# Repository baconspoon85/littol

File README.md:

# littol
3 row 30% katana with exploded spacebar

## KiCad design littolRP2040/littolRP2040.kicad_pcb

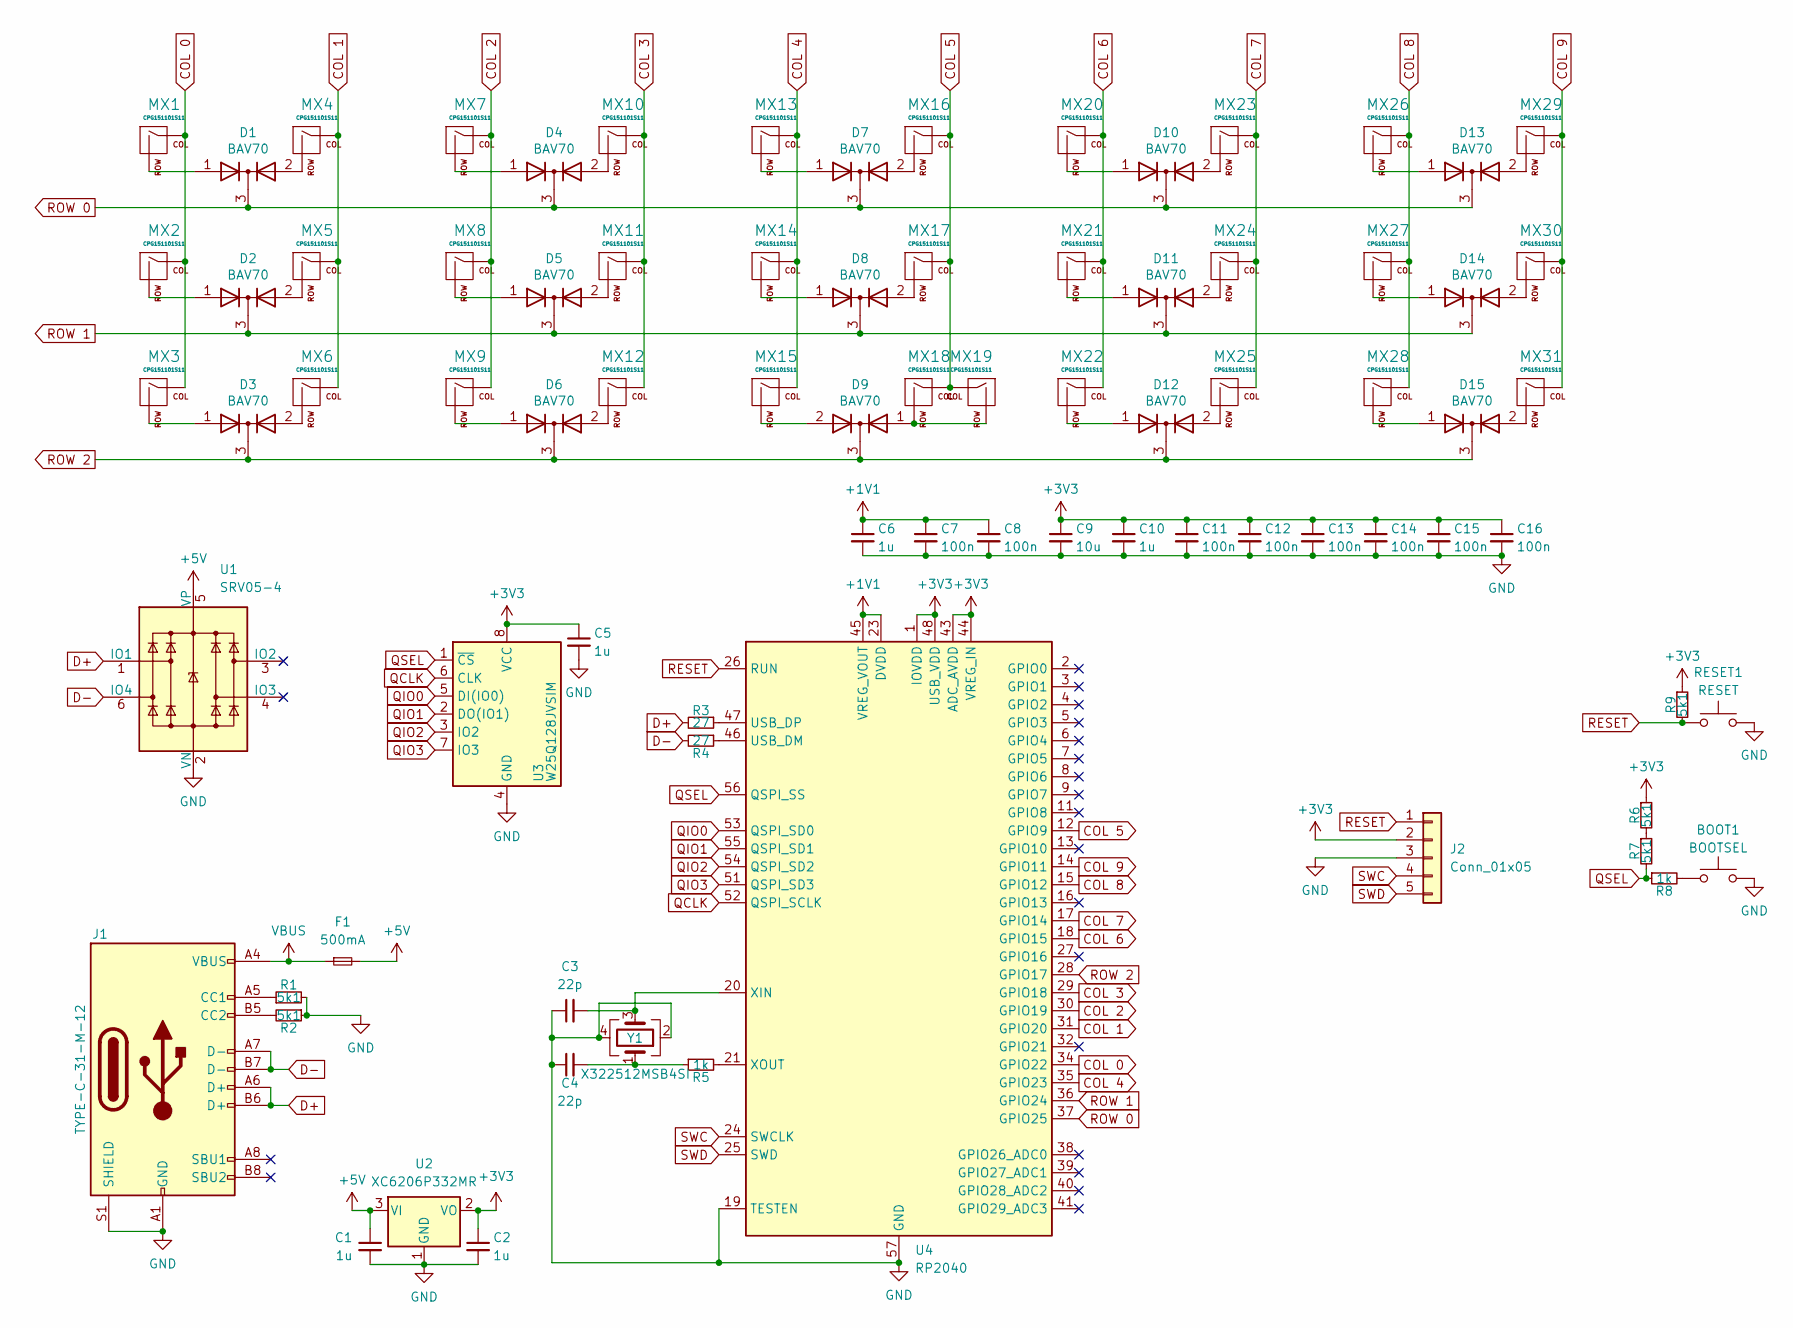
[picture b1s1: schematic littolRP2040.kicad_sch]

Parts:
BOOT1: BOOTSEL; SW_SPST_TL3342; LCSC C318884
C1, C2, C5, C6, C10: 1u; C_0402_1005Metric; LCSC C52923
C3, C4: 22p; C_0402_1005Metric; LCSC C1555
C7, C8, C11, C12, C13, C14, C15, C16: 100n; C_0402_1005Metric; LCSC C2655418
C9: 10u; C_0603_1608Metric; LCSC C19702
D1, D2, D3, D4, D5, D6, D7, D8, D9, D10, D11, D12, D13, D14, D15: BAV70; SOT-23; LCSC C2828461
F1: 500mA; Fuse_1206_3216Metric; LCSC C377237
J1: TYPE-C-31-M-12; USB_C_Receptacle_HRO_TYPE-C-31-M-12; LCSC C165948
J2: Conn_01x05; PinHeader_1x05_P2.54mm_Vertical
MX1, MX29: CPG151101S11; MXOnly-1.5U-Hotswap; LCSC C2803348
MX2, MX30: CPG151101S11; MXOnly-1.25U-Hotswap; LCSC C2803348
MX3, MX4, MX5, MX6, MX7, MX8, MX9, MX10, MX11, MX12, MX13, MX14, MX15, MX16, MX17, MX18, MX20, MX21, MX22, MX23, MX24, MX25, MX26, MX27, MX28, MX31: CPG151101S11; MXOnly-1U-Hotswap; LCSC C2803348
MX19: CPG151101S11; MXOnly-2U-Hotswap; LCSC C2803348
R1, R2, R6, R7, R9: 5k1; R_0402_1005Metric; LCSC C103086
R3, R4: 27; R_0402_1005Metric; LCSC C25100
R5, R8: 1k; R_0402_1005Metric; LCSC C279987
RESET1: RESET; SW_SPST_TL3342; LCSC C318884
U1: SRV05-4; SOT-23-6-routable; LCSC C2972082
U2: XC6206P332MR; SOT-23-3
U3: W25Q128JVSIM; SOIC-8_5.23x5.23mm_P1.27mm; LCSC C2613930
U4: RP2040; QFN-56-1EP_7x7mm_P0.4mm_EP3.2x3.2mm; LCSC C2040
Y1: X322512MSB4SI; Crystal_SMD_3225-4Pin_3.2x2.5mm; LCSC C9002

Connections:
+1V1: C6.1, C7.1, C8.1, U4.23 (DVDD), U4.45 (VREG_VOUT), U4.50 (DVDD)
+3V3: C2.1, C5.1, C9.1, C10.1, C11.1, C12.1, C13.1, C14.1, C15.1, C16.1, J2.2, R6.1, R9.1, U2.2 (VO), U3.8 (VCC), U4.1 (IOVDD), U4.10 (IOVDD), U4.22 (IOVDD), U4.33 (IOVDD), U4.42 (IOVDD), U4.43 (ADC_AVDD), U4.44 (VREG_IN), U4.48 (USB_VDD), U4.49 (IOVDD)
+5V: C1.1, F1.2, U1.5 (VP), U2.3 (VI)
COL 0: MX1.1 (COL), MX2.1 (COL), MX3.1 (COL), U4.34 (GPIO22)
COL 1: MX4.1 (COL), MX5.1 (COL), MX6.1 (COL), U4.31 (GPIO20)
COL 2: MX7.1 (COL), MX8.1 (COL), MX9.1 (COL), U4.30 (GPIO19)
COL 3: MX10.1 (COL), MX11.1 (COL), MX12.1 (COL), U4.29 (GPIO18)
COL 4: MX13.1 (COL), MX14.1 (COL), MX15.1 (COL), U4.35 (GPIO23)
COL 5: MX16.1 (COL), MX17.1 (COL), MX18.1 (COL), MX19.1 (COL), U4.12 (GPIO9)
COL 6: MX20.1 (COL), MX21.1 (COL), MX22.1 (COL), U4.18 (GPIO15)
COL 7: MX23.1 (COL), MX24.1 (COL), MX25.1 (COL), U4.17 (GPIO14)
COL 8: MX26.1 (COL), MX27.1 (COL), MX28.1 (COL), U4.15 (GPIO12)
COL 9: MX29.1 (COL), MX30.1 (COL), MX31.1 (COL), U4.14 (GPIO11)
D+: J1.A6 (D+), J1.B6 (D+), R3.2, U1.1 (IO1)
D-: J1.A7 (D-), J1.B7 (D-), R4.2, U1.6 (IO4)
GND: BOOT1.2, C1.2, C2.2, C3.1, C4.1, C5.2, C6.2, C7.2, C8.2, C9.2, C10.2, C11.2, C12.2, C13.2, C14.2, C15.2, C16.2, J1.A1 (GND), J1.A12 (GND), J1.B1 (GND), J1.B12 (GND), J1.S1 (SHIELD), J2.3, R1.2, R2.1, RESET1.2, U1.2 (VN), U2.1 (GND), U3.4 (GND), U4.19 (TESTEN), U4.57 (GND), Y1.2, Y1.4
unnamed: BOOT1.1, R8.2
unnamed: C4.2, R5.1, Y1.1
unnamed: J1.A5 (CC1), R1.1
unnamed: J1.B5 (CC2), R2.2
unnamed: D1.1 (A), MX1.2 (ROW)
unnamed: D2.1 (A), MX2.2 (ROW)
unnamed: D3.1 (A), MX3.2 (ROW)
unnamed: D1.2 (A), MX4.2 (ROW)
unnamed: D2.2 (A), MX5.2 (ROW)
unnamed: D3.2 (A), MX6.2 (ROW)
unnamed: D4.1 (A), MX7.2 (ROW)
unnamed: D5.1 (A), MX8.2 (ROW)
unnamed: D6.1 (A), MX9.2 (ROW)
unnamed: D4.2 (A), MX10.2 (ROW)
unnamed: D5.2 (A), MX11.2 (ROW)
unnamed: D6.2 (A), MX12.2 (ROW)
unnamed: D7.1 (A), MX13.2 (ROW)
unnamed: D8.1 (A), MX14.2 (ROW)
unnamed: D9.2 (A), MX15.2 (ROW)
unnamed: D7.2 (A), MX16.2 (ROW)
unnamed: D8.2 (A), MX17.2 (ROW)
unnamed: D9.1 (A), MX18.2 (ROW), MX19.2 (ROW)
unnamed: D10.1 (A), MX20.2 (ROW)
unnamed: D11.1 (A), MX21.2 (ROW)
unnamed: D12.1 (A), MX22.2 (ROW)
unnamed: D10.2 (A), MX23.2 (ROW)
unnamed: D11.2 (A), MX24.2 (ROW)
unnamed: D12.2 (A), MX25.2 (ROW)
unnamed: D13.1 (A), MX26.2 (ROW)
unnamed: D14.1 (A), MX27.2 (ROW)
unnamed: D15.1 (A), MX28.2 (ROW)
unnamed: D13.2 (A), MX29.2 (ROW)
unnamed: D14.2 (A), MX30.2 (ROW)
unnamed: D15.2 (A), MX31.2 (ROW)
unnamed: R6.2, R7.1
unnamed: R4.1, U4.46 (USB_DM)
unnamed: R3.1, U4.47 (USB_DP)
unnamed: C3.2, U4.20 (XIN), Y1.3
unnamed: R5.2, U4.21 (XOUT)
QCLK: U3.6 (CLK), U4.52 (QSPI_SCLK)
QIO0: U3.5 (DI(IO0)), U4.53 (QSPI_SD0)
QIO1: U3.2 (DO(IO1)), U4.55 (QSPI_SD1)
QIO2: U3.3 (IO2), U4.54 (QSPI_SD2)
QIO3: U3.7 (IO3), U4.51 (QSPI_SD3)
QSEL: R7.2, R8.1, U3.1 (~CS), U4.56 (QSPI_SS)
RESET: J2.1, R9.2, RESET1.1, U4.26 (RUN)
ROW 0: D1.3 (K), D4.3 (K), D7.3 (K), D10.3 (K), D13.3 (K), U4.37 (GPIO25)
ROW 1: D2.3 (K), D5.3 (K), D8.3 (K), D11.3 (K), D14.3 (K), U4.36 (GPIO24)
ROW 2: D3.3 (K), D6.3 (K), D9.3 (K), D12.3 (K), D15.3 (K), U4.28 (GPIO17)
SWC: J2.4, U4.24 (SWCLK)
SWD: J2.5, U4.25 (SWD)
VBUS: F1.1, J1.A4 (VBUS), J1.A9 (VBUS), J1.B4 (VBUS), J1.B9 (VBUS)

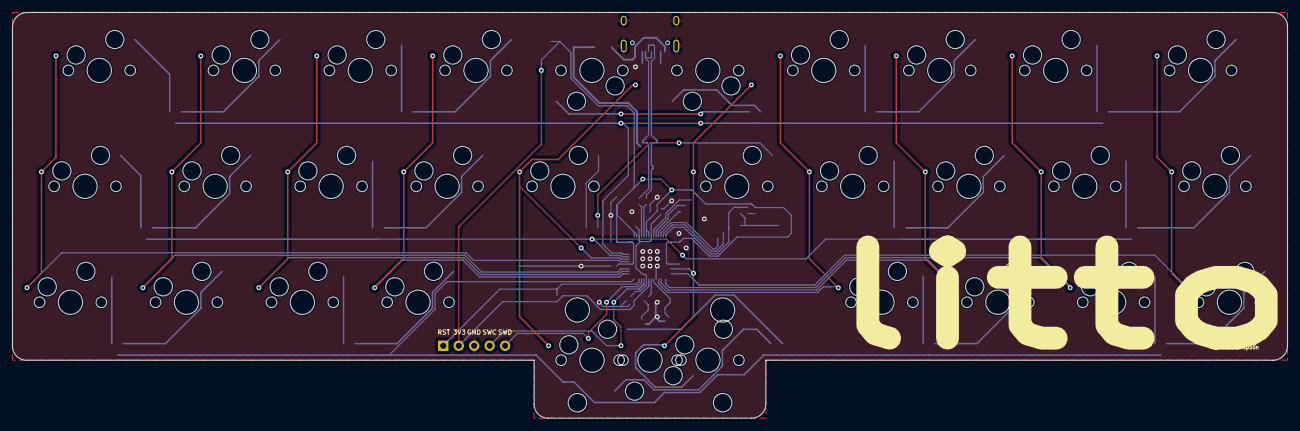
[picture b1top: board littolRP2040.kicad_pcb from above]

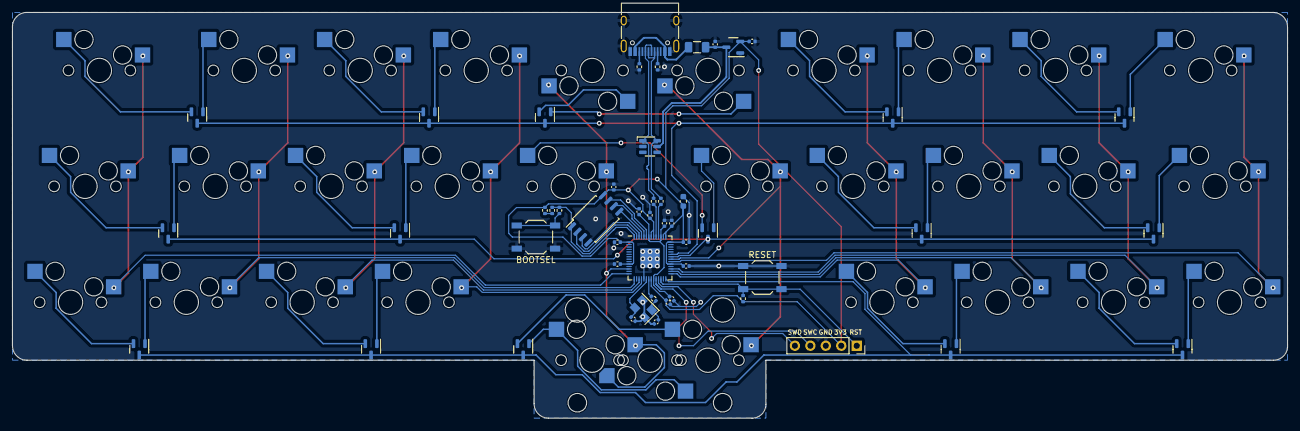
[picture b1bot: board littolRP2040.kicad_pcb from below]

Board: 2 copper layers, 209.6 x 66.7 mm, 81 parts (80 on the bottom side), 68 nets.

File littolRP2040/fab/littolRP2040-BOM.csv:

Comment,Designator,Footprint,JLCPCB Part#(optional)
BOOTSEL,BOOT1,Button_Switch_SMD:SW_SPST_TL3342,C318884
1uF,C1,Capacitor_SMD:C_0402_1005Metric,C52923
1uF,C2,Capacitor_SMD:C_0402_1005Metric,C52923
22pF,C3,Capacitor_SMD:C_0402_1005Metric,C1555
22pF,C4,Capacitor_SMD:C_0402_1005Metric,C1555
1uF,C5,Capacitor_SMD:C_0402_1005Metric,C52923
1uF,C6,Capacitor_SMD:C_0402_1005Metric,C52923
0.1uF,C7,Capacitor_SMD:C_0402_1005Metric,C2655418
0.1uF,C8,Capacitor_SMD:C_0402_1005Metric,C2655418
10uF,C9,Capacitor_SMD:C_0603_1608Metric,C19702
1uF,C10,Capacitor_SMD:C_0402_1005Metric,C52923
0.1uF,C11,Capacitor_SMD:C_0402_1005Metric,C2655418
0.1uF,C12,Capacitor_SMD:C_0402_1005Metric,C2655418
0.1uF,C13,Capacitor_SMD:C_0402_1005Metric,C2655418
0.1uF,C14,Capacitor_SMD:C_0402_1005Metric,C2655418
0.1uF,C15,Capacitor_SMD:C_0402_1005Metric,C2655418
0.1uF,C16,Capacitor_SMD:C_0402_1005Metric,C2655418
BAV70,D1,Package_TO_SOT_SMD:SOT-23,C2828461
BAV70,D2,Package_TO_SOT_SMD:SOT-23,C2828461
BAV70,D3,Package_TO_SOT_SMD:SOT-23,C2828461
BAV70,D4,Package_TO_SOT_SMD:SOT-23,C2828461
BAV70,D5,Package_TO_SOT_SMD:SOT-23,C2828461
BAV70,D6,Package_TO_SOT_SMD:SOT-23,C2828461
BAV70,D7,Package_TO_SOT_SMD:SOT-23,C2828461
BAV70,D8,Package_TO_SOT_SMD:SOT-23,C2828461
BAV70,D9,Package_TO_SOT_SMD:SOT-23,C2828461
BAV70,D10,Package_TO_SOT_SMD:SOT-23,C2828461
BAV70,D11,Package_TO_SOT_SMD:SOT-23,C2828461
BAV70,D12,Package_TO_SOT_SMD:SOT-23,C2828461
BAV70,D13,Package_TO_SOT_SMD:SOT-23,C2828461
BAV70,D14,Package_TO_SOT_SMD:SOT-23,C2828461
BAV70,D15,Package_TO_SOT_SMD:SOT-23,C2828461
500mA,F1,Fuse:Fuse_1206_3216Metric,C377237
CPG151101S11,MX1,MX_Only:MXOnly-1.5U-Hotswap,C2803348
CPG151101S11,MX2,MX_Only:MXOnly-1.25U-Hotswap,C2803348
CPG151101S11,MX3,MX_Only:MXOnly-1U-Hotswap,C2803348
CPG151101S11,MX4,MX_Only:MXOnly-1U-Hotswap,C2803348
CPG151101S11,MX5,MX_Only:MXOnly-1U-Hotswap,C2803348
CPG151101S11,MX6,MX_Only:MXOnly-1U-Hotswap,C2803348
CPG151101S11,MX7,MX_Only:MXOnly-1U-Hotswap,C2803348
CPG151101S11,MX8,MX_Only:MXOnly-1U-Hotswap,C2803348
CPG151101S11,MX9,MX_Only:MXOnly-1U-Hotswap,C2803348
CPG151101S11,MX10,MX_Only:MXOnly-1U-Hotswap,C2803348
CPG151101S11,MX11,MX_Only:MXOnly-1U-Hotswap,C2803348
CPG151101S11,MX12,MX_Only:MXOnly-1U-Hotswap,C2803348
CPG151101S11,MX13,MX_Only:MXOnly-1U-Hotswap,C2803348
CPG151101S11,MX14,MX_Only:MXOnly-1U-Hotswap,C2803348
CPG151101S11,MX15,MX_Only:MXOnly-1U-Hotswap,C2803348
CPG151101S11,MX16,MX_Only:MXOnly-1U-Hotswap,C2803348
CPG151101S11,MX17,MX_Only:MXOnly-1U-Hotswap,C2803348
CPG151101S11,MX18,MX_Only:MXOnly-1U-Hotswap,C2803348
CPG151101S11,MX19,MX_Only:MXOnly-2U-Hotswap,C2803348
CPG151101S11,MX20,MX_Only:MXOnly-1U-Hotswap,C2803348
CPG151101S11,MX21,MX_Only:MXOnly-1U-Hotswap,C2803348
CPG151101S11,MX22,MX_Only:MXOnly-1U-Hotswap,C2803348
CPG151101S11,MX23,MX_Only:MXOnly-1U-Hotswap,C2803348
CPG151101S11,MX24,MX_Only:MXOnly-1U-Hotswap,C2803348
CPG151101S11,MX25,MX_Only:MXOnly-1U-Hotswap,C2803348
CPG151101S11,MX26,MX_Only:MXOnly-1U-Hotswap,C2803348
CPG151101S11,MX27,MX_Only:MXOnly-1U-Hotswap,C2803348
CPG151101S11,MX28,MX_Only:MXOnly-1U-Hotswap,C2803348
CPG151101S11,MX29,MX_Only:MXOnly-1.5U-Hotswap,C2803348
CPG151101S11,MX30,MX_Only:MXOnly-1.25U-Hotswap,C2803348
CPG151101S11,MX31,MX_Only:MXOnly-1U-Hotswap,C2803348
5k1,R1,Resistor_SMD:R_0402_1005Metric,C103086
5k1,R2,Resistor_SMD:R_0402_1005Metric,C103086
27,R3,Resistor_SMD:R_0402_1005Metric,C25100
27,R4,Resistor_SMD:R_0402_1005Metric,C25100
1k,R5,Resistor_SMD:R_0402_1005Metric,C279987
5k1,R6,Resistor_SMD:R_0402_1005Metric,C103086
5k1,R7,Resistor_SMD:R_0402_1005Metric,C103086
1k,R8,Resistor_SMD:R_0402_1005Metric,C279987
5k1,R9,Resistor_SMD:R_0402_1005Metric,C103086
RESET,RESET1,Button_Switch_SMD:SW_SPST_TL3342,C318884
SRV05-4,U1,PCM_marbastlib-various:SOT-23-6-routable,C2972082
XC6206P332MR,U2,Package_TO_SOT_SMD:SOT-23-3,C5446
W25Q128JVSIM,U3,Package_SO:SOIC-8_5.23x5.23mm_P1.27mm,C2613930
RP2040,U4,Package_DFN_QFN:QFN-56-1EP_7x7mm_P0.4mm_EP3.2x3.2mm,C2040
X322512MSB4SI,Y1,Crystal:Crystal_SMD_3225-4Pin_3.2x2.5mm,C9002

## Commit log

2023-07-07 uploaded complete file
    case needs usb port figured, perhaps redo screw positioning
2023-07-07 Update README.md
    pictor
2023-07-07 uploded .step for 3d printing
2023-07-07 Delete littol for 3dp.step
    need to change hole size rq
2023-07-07 3dp case with inserts
2023-07-07 plate for littol
2023-07-12 Initial commit for littol PCB
    Untested PCB for littol by OBABO. Fab files are gerbers, drill, and drill map for JLCPCB. BOM still needs to be generated.
2023-07-17 PCB cleanup. Updated fabrication files. Added BOM and position files for JLCPCB fabrication.
2023-10-29 firmware
